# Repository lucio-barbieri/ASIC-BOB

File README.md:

# ASIC-BOB

Break-out board for the RFID+ ASIC.

---

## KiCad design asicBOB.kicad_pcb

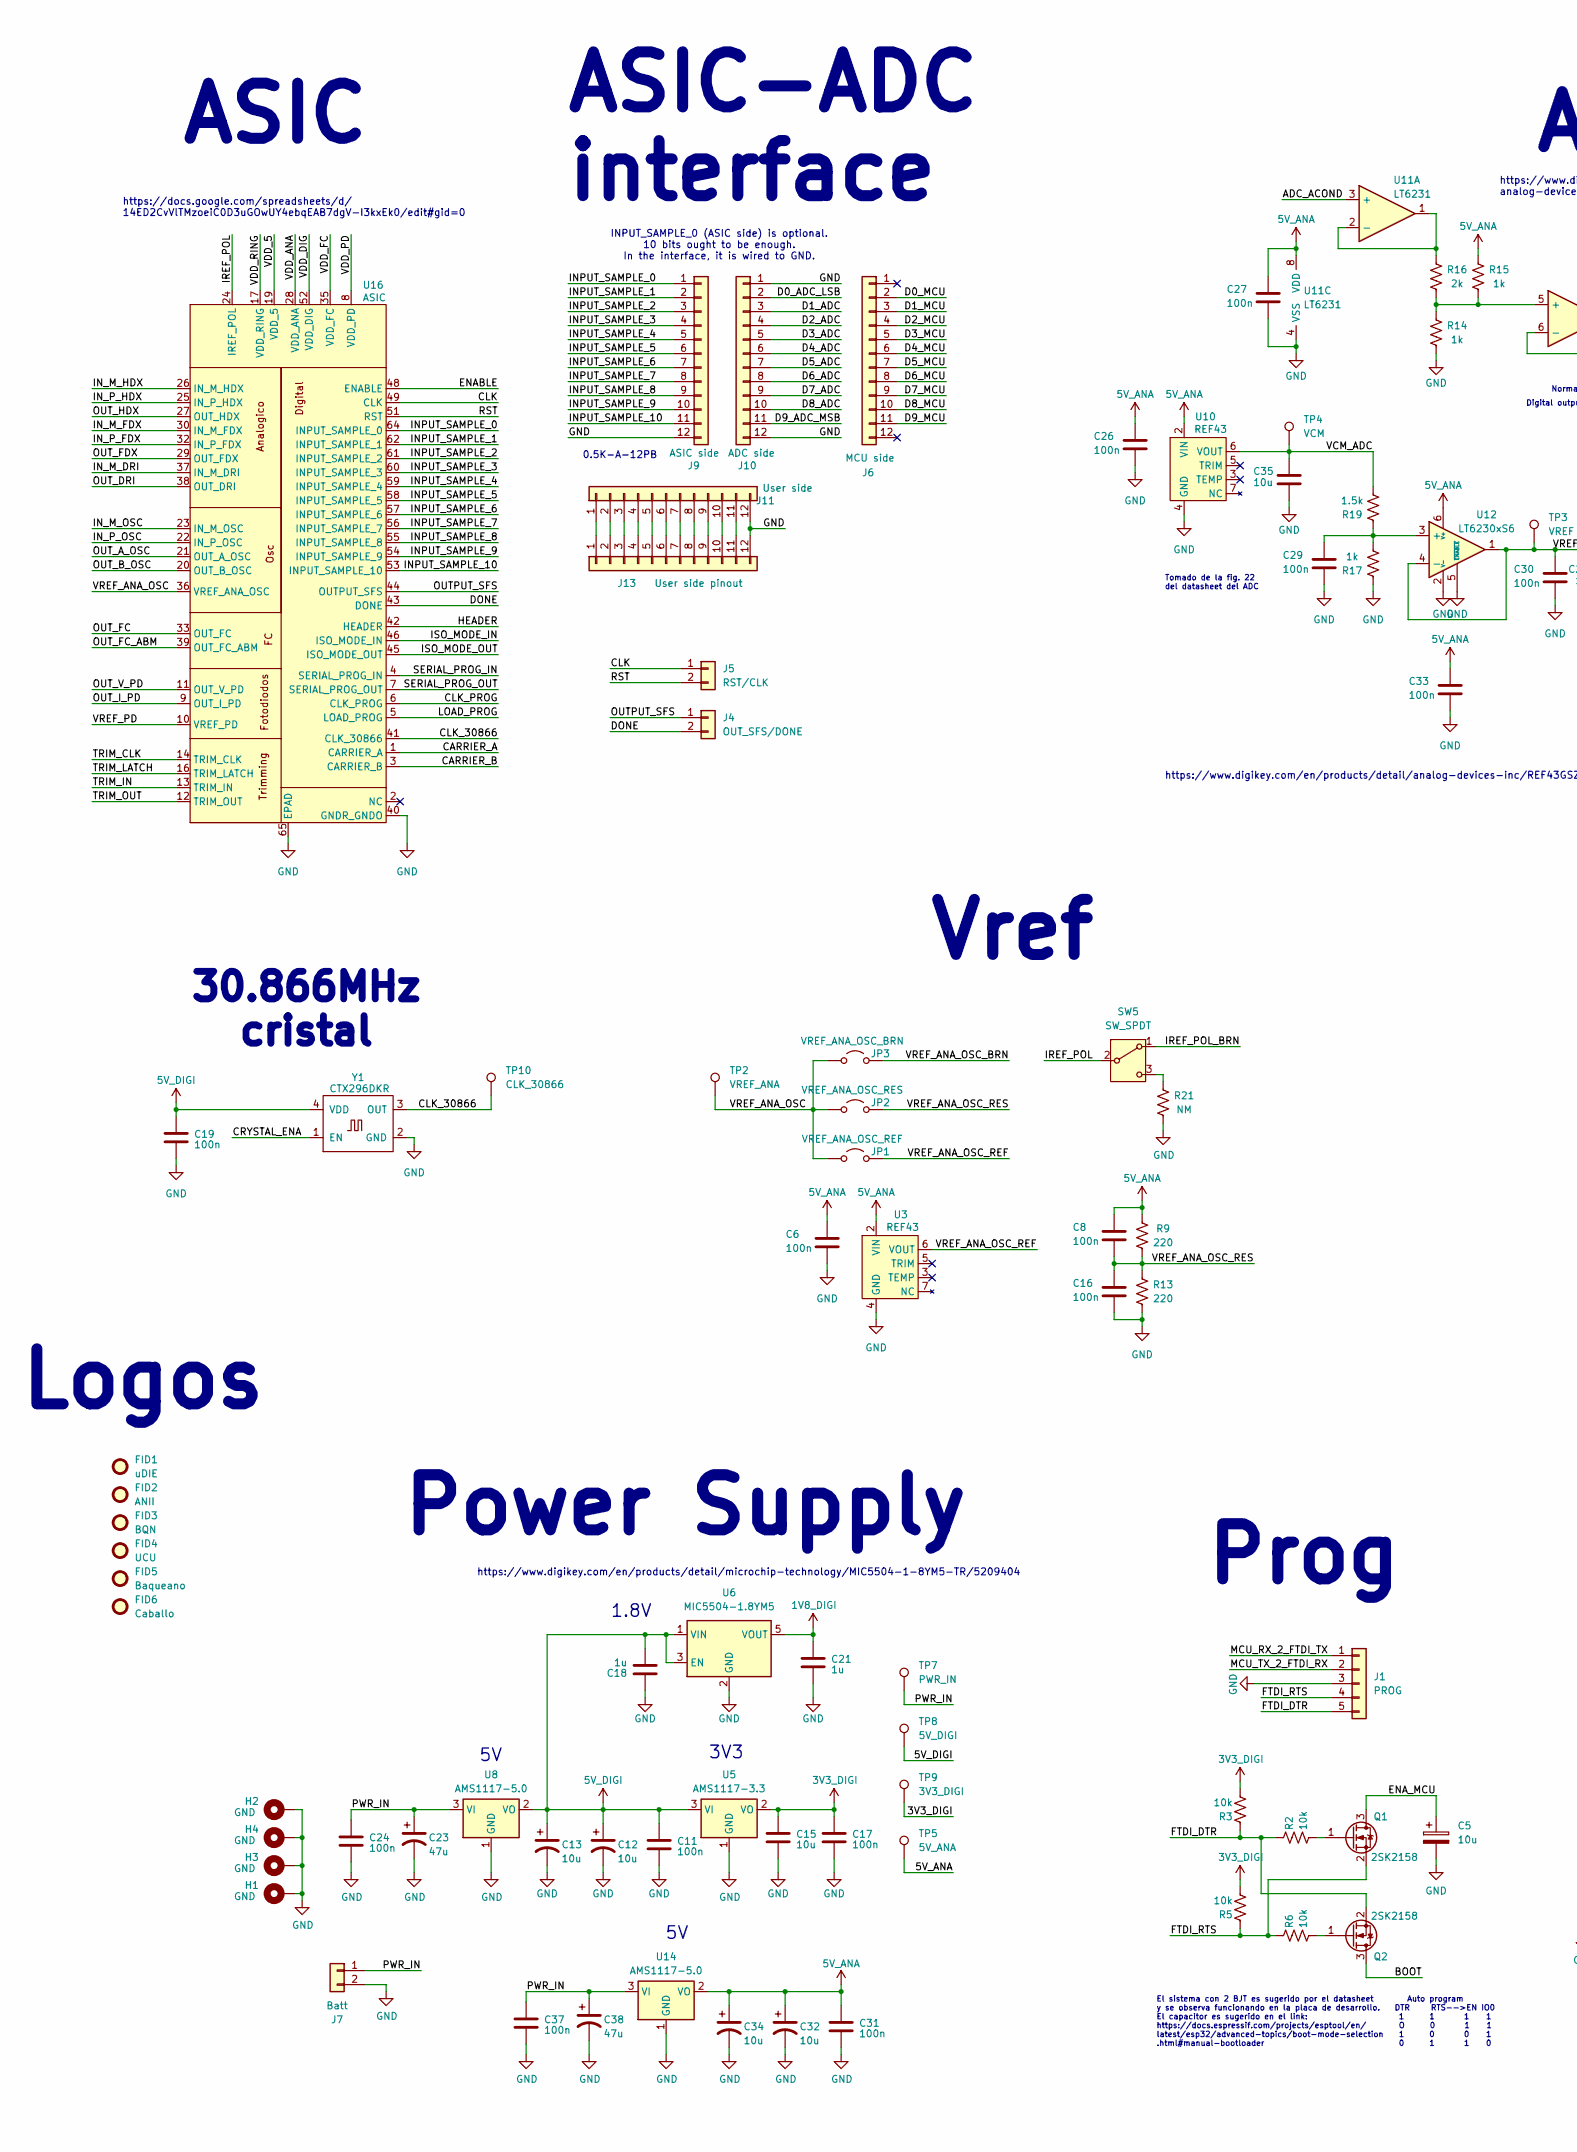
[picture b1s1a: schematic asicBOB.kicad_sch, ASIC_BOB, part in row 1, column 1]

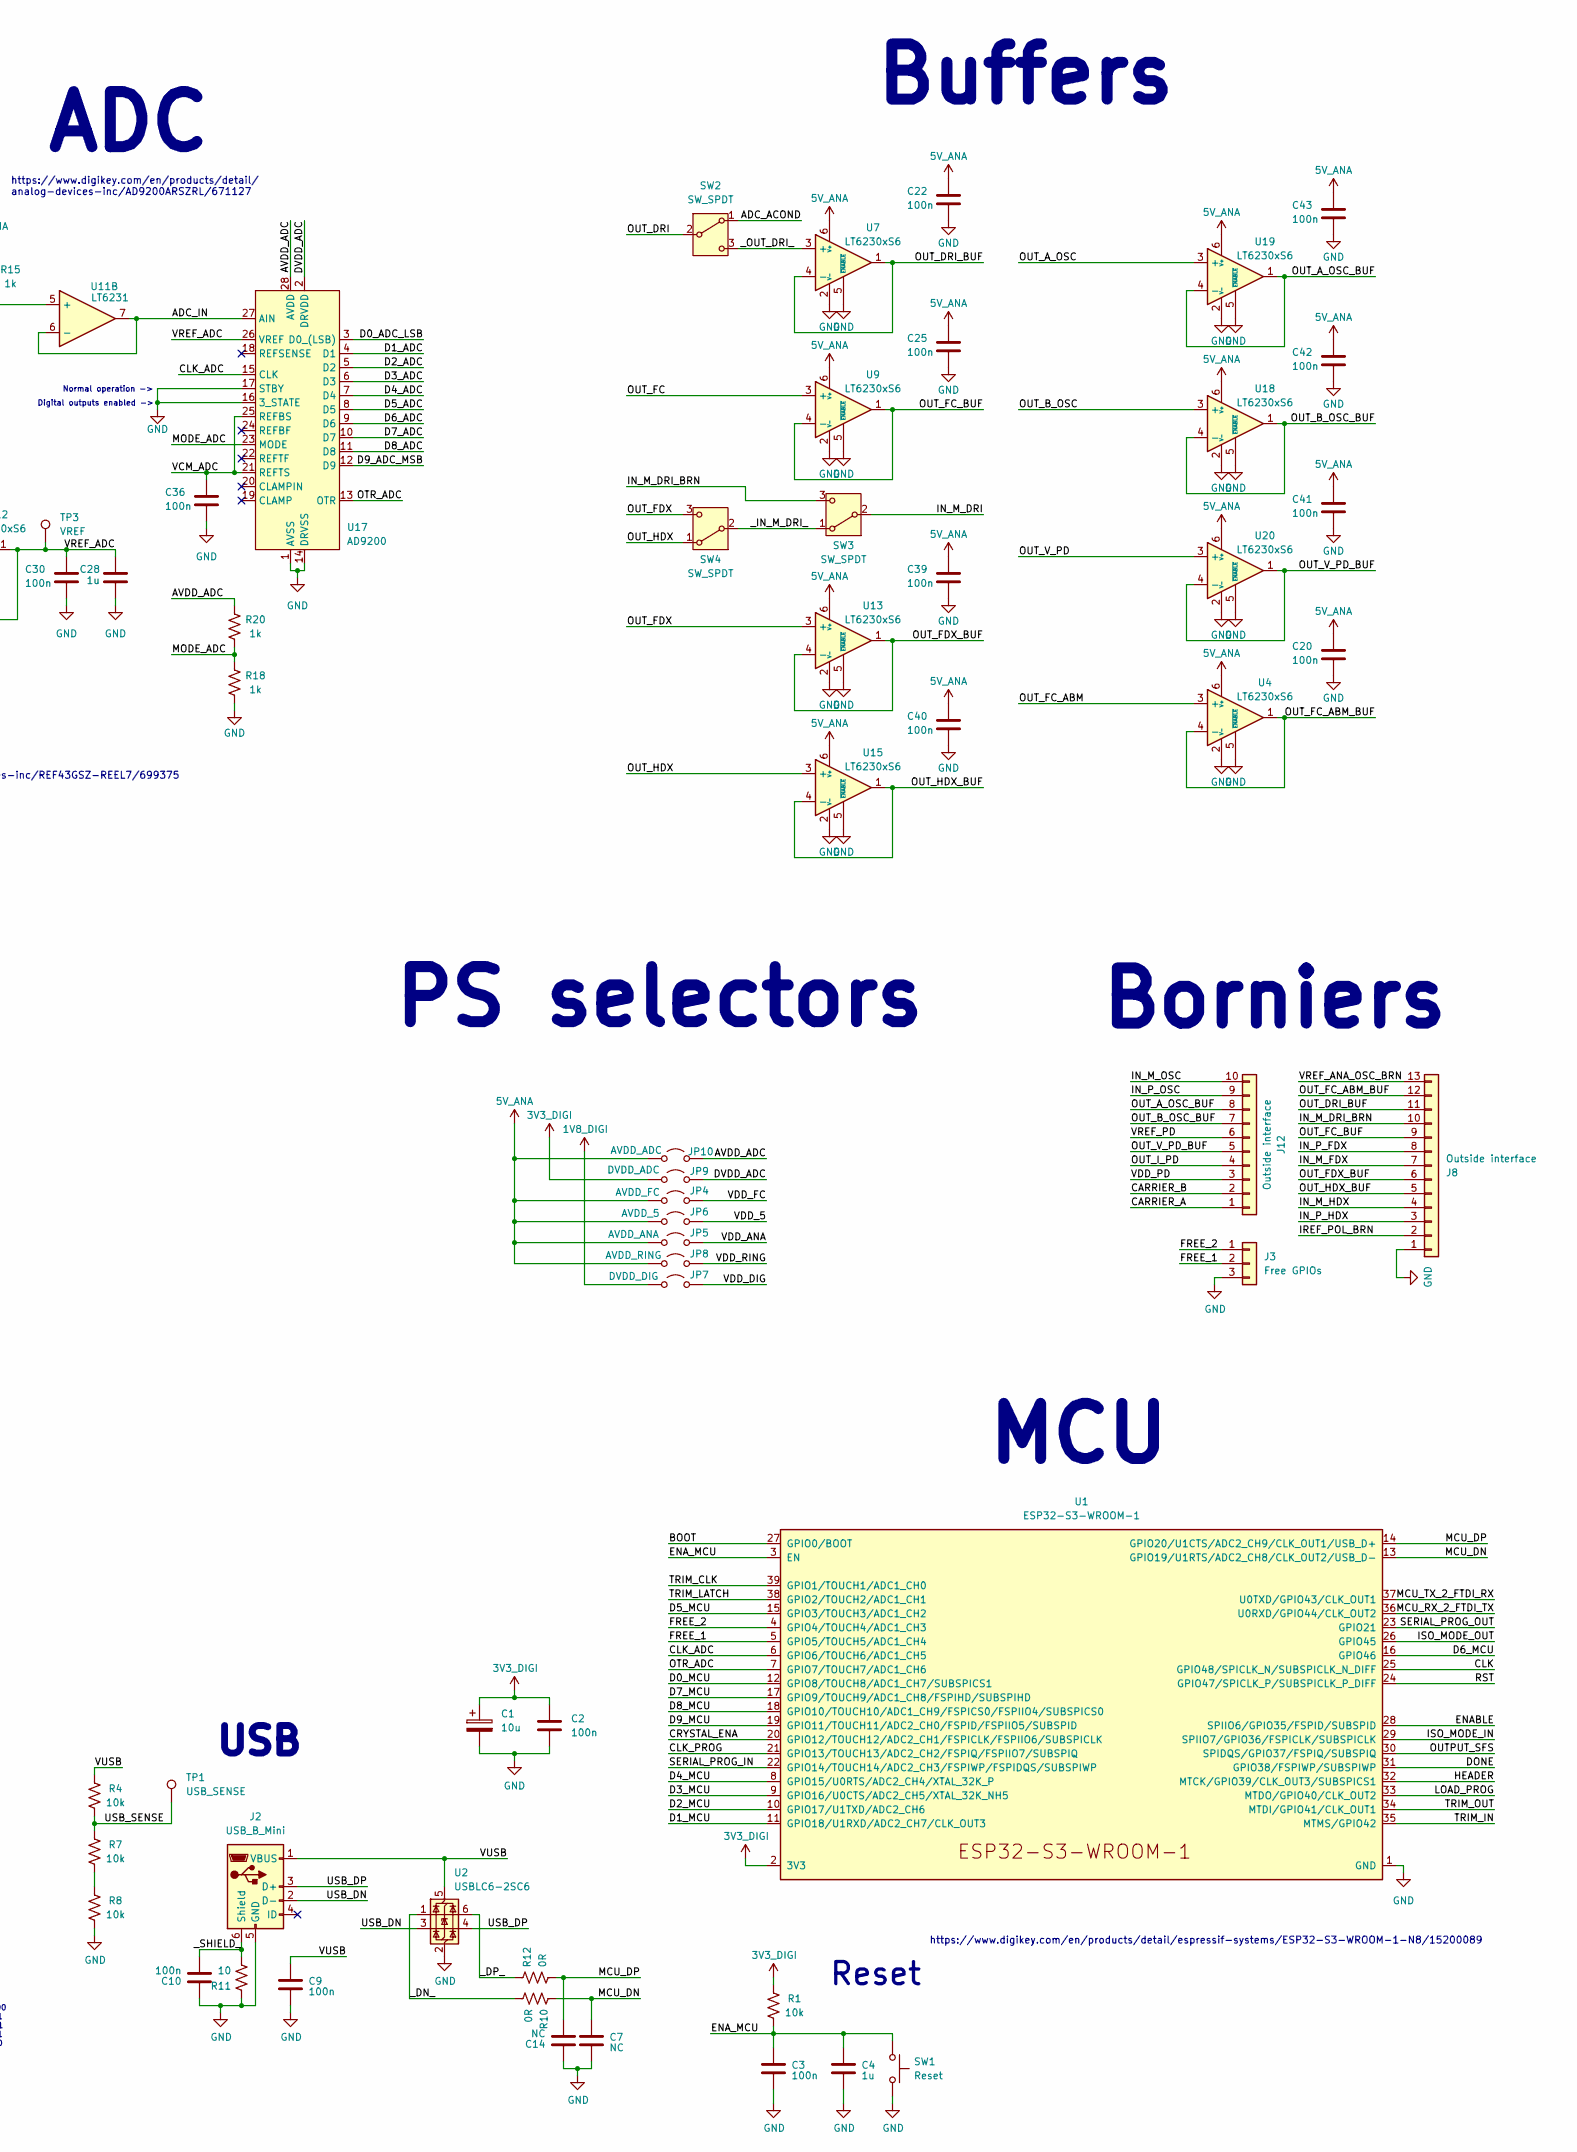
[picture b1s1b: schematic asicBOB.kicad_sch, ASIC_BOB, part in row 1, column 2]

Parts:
C1, C12, C13, C15, C32, C34, C35: 10u; C_0603_1608Metric
C2, C3, C6, C8, C9, C10, C11, C16, C17, C19, C20, C22, C24, C25, C26, C27, C29, C30, C31, C33, C36, C37, C39, C40, C41, C42, C43: 100n; C_0603_1608Metric
C4, C18, C21, C28: 1u; C_0603_1608Metric
C5: 10u; C_1206_3216Metric
C7, C14: NC; C_0603_1608Metric
C23, C38: 47u; C_0805_2012Metric
FID1: uDIE; Logo_uDIE
FID2: ANII; Logo_ANII
FID3: BQN; Logo_BQN_12x4
FID4: UCU; Logo_UCU
FID5: Baqueano; Logo_baqueano_5x25
FID6: Caballo; Logo_caballoConBoina_15mm
H1, H2, H3, H4: GND; MountingHole_2.2mm_M2_Pad_Via
J1: PROG; PinSocket_1x05_P2.54mm_Vertical
J2: USB_B_Mini; USB_Mini-B_Lumberg_2486_01_Horizontal
J3: Free GPIOs; PinHeader_1x03_P2.54mm_Vertical
J4: OUT_SFS/DONE; PinHeader_1x02_P1.27mm_Vertical
J5: RST/CLK; PinHeader_1x02_P1.27mm_Vertical
J6: MCU side; 117347422
J7: Batt; TerminalBlock_Phoenix_MKDS-1,5-2_1x02_P5.00mm_Horizontal
J8: Outside interface; TerminalBlock_Phoenix_MKDS-1,5-13-5.08_1x13_P5.08mm_Horizon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
J9: ASIC side; 117347422
J10: ADC side; 117347422
J11: User side; 117347422
J12: Outside interface; TerminalBlock_Phoenix_MKDS-1,5-10-5.08_1x10_P5.08mm_Horizon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
J13: User side pinout; PinHeader_1x12_P2.54mm_Vertical
JP1: VREF_ANA_OSC_REF; PinHeader_1x02_P2.54mm_Vertical
JP2: VREF_ANA_OSC_RES; PinHeader_1x02_P2.54mm_Vertical
JP3: VREF_ANA_OSC_BRN; PinHeader_1x02_P2.54mm_Vertical
JP4: AVDD_FC; PinHeader_1x02_P2.54mm_Vertical
JP5: AVDD_ANA; PinHeader_1x02_P2.54mm_Vertical
JP6: AVDD_5; PinHeader_1x02_P2.54mm_Vertical
JP7: DVDD_DIG; PinHeader_1x02_P2.54mm_Vertical
JP8: AVDD_RING; PinHeader_1x02_P2.54mm_Vertical
JP9: DVDD_ADC; PinHeader_1x02_P2.54mm_Vertical
JP10: AVDD_ADC; PinHeader_1x02_P2.54mm_Vertical
Q1, Q2: 2SK2158; SOT-23
R1, R2, R3, R4, R5, R6, R7, R8: 10k; R_0603_1608Metric
R9, R13: 220; R_0603_1608Metric
R10, R12: 0R; R_0603_1608Metric
R11: 10; R_0603_1608Metric
R14, R15, R17, R18, R20: 1k; R_0603_1608Metric
R16: 2k; R_0603_1608Metric
R19: 1.5k; R_0603_1608Metric
R21: NM; R_0603_1608Metric
SW1: Reset; SW_Push_1P1T_NO_6x6mm_H9.5mm
SW2, SW3, SW4, SW5: SW_SPDT; PinHeader_1x03_P2.54mm_Vertical
TP1: USB_SENSE; TestPoint_Pad_D1.0mm
TP2: VREF_ANA; TestPoint_Pad_D1.0mm
TP3: VREF; TestPoint_Pad_D1.0mm
TP4: VCM; TestPoint_Pad_D1.0mm
TP5: 5V_ANA; TestPoint_Pad_D1.0mm
TP7: PWR_IN; TestPoint_Pad_D1.0mm
TP8: 5V_DIGI; TestPoint_Pad_D1.0mm
TP9: 3V3_DIGI; TestPoint_Pad_D1.0mm
TP10: CLK_30866; TestPoint_Pad_D1.0mm
U1: ESP32-S3-WROOM-1
U2: USBLC6-2SC6; SOT-23-6
U3, U10: REF43; SOIC-8_3.9x4.9mm_P1.27mm
U4, U7, U9, U12, U13, U15, U18, U19, U20: LT6230xS6; TSOT-23-6
U5: AMS1117-3.3; SOT-223-3_TabPin2
U6: MIC5504-1.8YM5; SOT-23-5
U8, U14: AMS1117-5.0; SOT-223-3_TabPin2
U11: LT6231; SO-8_5.3x6.2mm_P1.27mm
U16: ASIC; ASIC_RFID
U17: AD9200; SSOP-28_5.3x10.2mm_P0.65mm
Y1: CTX296DKR

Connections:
1V8_DIGI: C21.1, JP7.2 (B), U6.5 (VOUT)
3V3_DIGI: C1.1, C2.1, C15.1, C17.1, JP9.2 (B), R1.2, R3.2, R5.2, TP9.1, U1.2 (3V3), U5.2 (VO)
5V_ANA: C6.2, C8.2, C20.2, C22.2, C25.2, C26.2, C27.2, C31.1, C32.1, C33.2, C34.1, C39.2, C40.2, C41.2, C42.2, C43.2, JP4.2 (B), JP5.2 (B), JP6.2 (B), JP8.2 (B), JP10.1 (A), R9.2, R15.2, TP5.1, U3.2 (VIN), U4.6 (V+), U7.6 (V+), U9.6 (V+), U10.2 (VIN), U11.8 (VDD), U12.6 (V+), U13.6 (V+), U14.2 (VO), U15.6 (V+), U18.6 (V+), U19.6 (V+), U20.6 (V+)
5V_DIGI: C11.1, C12.1, C13.1, C18.2, C19.1, TP8.1, U5.3 (VI), U6.1 (VIN), U6.3 (EN), U8.2 (VO), Y1.4 (VDD)
/ADC_ACOND: SW2.1 (A), U11.3 (+)
/ADC_IN: U11.6 (-), U11.7, U17.27 (AIN)
/AVDD_ADC: JP10.2 (B), R20.2, U17.28 (AVDD)
/BOOT: Q2.3 (D), U1.27 (GPIO0/BOOT)
/CARRIER_A: J12.1, U16.1 (CARRIER_A)
/CARRIER_B: J12.2, U16.3 (CARRIER_B)
/CLK: J5.1, U1.25 (GPIO48/SPICLK_N/SUBSPICLK_N_DIFF), U16.49 (CLK)
/CLK_30866: TP10.1, U16.41 (CLK_30866), Y1.3 (OUT)
/CLK_ADC: U1.6 (GPIO6/TOUCH6/ADC1_CH5), U17.15 (CLK)
/CLK_PROG: U1.21 (GPIO13/TOUCH13/ADC2_CH2/FSPIQ/FSPIIO7/S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), U16.6 (CLK_PROG)
/CRYSTAL_ENA: U1.20 (GPIO12/TOUCH12/ADC2_CH1/FSPICLK/FSPIIO6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), Y1.1 (EN)
/D0_ADC_LSB: J10.2, U17.3 (D0_(LSB))
/D0_MCU: J6.2, U1.12 (GPIO8/TOUCH8/ADC1_CH7/SUBSPICS1)
/D1_ADC: J10.3, U17.4 (D1)
/D1_MCU: J6.3, U1.11 (GPIO18/U1RXD/ADC2_CH7/CLK_OUT3)
/D2_ADC: J10.4, U17.5 (D2)
/D2_MCU: J6.4, U1.10 (GPIO17/U1TXD/ADC2_CH6)
/D3_ADC: J10.5, U17.6 (D3)
/D3_MCU: J6.5, U1.9 (GPIO16/U0CTS/ADC2_CH5/XTAL_32K_NH5)
/D4_ADC: J10.6, U17.7 (D4)
/D4_MCU: J6.6, U1.8 (GPIO15/U0RTS/ADC2_CH4/XTAL_32K_P)
/D5_ADC: J10.7, U17.8 (D5)
/D5_MCU: J6.7, U1.15 (GPIO3/TOUCH3/ADC1_CH2)
/D6_ADC: J10.8, U17.9 (D6)
/D6_MCU: J6.8, U1.16 (GPIO46)
/D7_ADC: J10.9, U17.10 (D7)
/D7_MCU: J6.9, U1.17 (GPIO9/TOUCH9/ADC1_CH8/FSPIHD/SUBSPIHD)
/D8_ADC: J10.10, U17.11 (D8)
/D8_MCU: J6.10, U1.18 (GPIO10/TOUCH10/ADC1_CH9/FSPICS0/FSPIIO4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)
/D9_ADC_MSB: J10.11, U17.12 (D9)
/D9_MCU: J6.11, U1.19 (GPIO11/TOUCH11/ADC2_CH0/FSPID/FSPIIO5/S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)
/DONE: J4.2, U1.31 (GPIO38/FSPIWP/SUBSPIWP), U16.43 (DONE)
/DVDD_ADC: JP9.1 (A), U17.2 (DRVDD)
/ENABLE: U1.28 (SPIIO6/GPIO35/FSPID/SUBSPID), U16.48 (ENABLE)
/ENA_MCU: C3.1, C4.1, C5.1, Q1.3 (D), R1.1, SW1.1, U1.3 (EN)
/FREE_1: J3.2, U1.5 (GPIO5/TOUCH5/ADC1_CH4)
/FREE_2: J3.1, U1.4 (GPIO4/TOUCH4/ADC1_CH3)
/FTDI_DTR: J1.5, Q2.2 (S), R2.1, R3.1
/FTDI_RTS: J1.4, Q1.2 (S), R5.1, R6.1
/HEADER: U1.32 (MTCK/GPIO39/CLK_OUT3/SUBSPICS1), U16.42 (HEADER)
/INPUT_SAMPLE_0: J9.1, U16.64 (INPUT_SAMPLE_0)
/INPUT_SAMPLE_1: J9.2, U16.62 (INPUT_SAMPLE_1)
/INPUT_SAMPLE_2: J9.3, U16.61 (INPUT_SAMPLE_2)
/INPUT_SAMPLE_3: J9.4, U16.60 (INPUT_SAMPLE_3)
/INPUT_SAMPLE_4: J9.5, U16.59 (INPUT_SAMPLE_4)
/INPUT_SAMPLE_5: J9.6, U16.58 (INPUT_SAMPLE_5)
/INPUT_SAMPLE_6: J9.7, U16.57 (INPUT_SAMPLE_6)
/INPUT_SAMPLE_7: J9.8, U16.56 (INPUT_SAMPLE_7)
/INPUT_SAMPLE_8: J9.9, U16.55 (INPUT_SAMPLE_8)
/INPUT_SAMPLE_9: J9.10, U16.54 (INPUT_SAMPLE_9)
/INPUT_SAMPLE_10: J9.11, U16.53 (INPUT_SAMPLE_10)
/IN_M_DRI: SW3.2 (B), U16.37 (IN_M_DRI)
/IN_M_DRI_BRN: J8.10, SW3.3 (C)
/IN_M_FDX: J8.7, U16.30 (IN_M_FDX)
/IN_M_HDX: J8.4, U16.26 (IN_M_HDX)
/IN_M_OSC: J12.10, U16.23 (IN_M_OSC)
/IN_P_FDX: J8.8, U16.32 (IN_P_FDX)
/IN_P_HDX: J8.3, U16.25 (IN_P_HDX)
/IN_P_OSC: J12.9, U16.22 (IN_P_OSC)
/IREF_POL: SW5.2 (B), U16.24 (IREF_POL)
/IREF_POL_BRN: J8.2, SW5.1 (A)
/ISO_MODE_IN: U1.29 (SPIIO7/GPIO36/FSPICLK/SUBSPICLK), U16.46 (ISO_MODE_IN)
/ISO_MODE_OUT: U1.26 (GPIO45), U16.45 (ISO_MODE_OUT)
/LOAD_PROG: U1.33 (MTDO/GPIO40/CLK_OUT2), U16.5 (LOAD_PROG)
/MCU_DN: C7.1, R10.1, U1.13 (GPIO19/U1RTS/ADC2_CH8/CLK_OUT2/USB_D-)
/MCU_DP: C14.2, R12.2, U1.14 (GPIO20/U1CTS/ADC2_CH9/CLK_OUT1/USB_D+)
/MCU_RX_2_FTDI_TX: J1.1, U1.36 (U0RXD/GPIO44/CLK_OUT2)
/MCU_TX_2_FTDI_RX: J1.2, U1.37 (U0TXD/GPIO43/CLK_OUT1)
/MODE_ADC: R18.2, R20.1, U17.23 (MODE)
/OTR_ADC: U1.7 (GPIO7/TOUCH7/ADC1_CH6), U17.13 (OTR)
/OUTPUT_SFS: J4.1, U1.30 (SPIDQS/GPIO37/FSPIQ/SUBSPIQ), U16.44 (OUTPUT_SFS)
/OUT_A_OSC: U16.21 (OUT_A_OSC), U19.3 (+)
/OUT_A_OSC_BUF: J12.8, U19.1, U19.4 (-)
/OUT_B_OSC: U16.20 (OUT_B_OSC), U18.3 (+)
/OUT_B_OSC_BUF: J12.7, U18.1, U18.4 (-)
/OUT_DRI: SW2.2 (B), U16.38 (OUT_DRI)
/OUT_DRI_BUF: J8.11, U7.1, U7.4 (-)
/OUT_FC: U9.3 (+), U16.33 (OUT_FC)
/OUT_FC_ABM: U4.3 (+), U16.39 (OUT_FC_ABM)
/OUT_FC_ABM_BUF: J8.12, U4.1, U4.4 (-)
/OUT_FC_BUF: J8.9, U9.1, U9.4 (-)
/OUT_FDX: SW4.3 (C), U13.3 (+), U16.29 (OUT_FDX)
/OUT_FDX_BUF: J8.6, U13.1, U13.4 (-)
/OUT_HDX: SW4.1 (A), U15.3 (+), U16.27 (OUT_HDX)
/OUT_HDX_BUF: J8.5, U15.1, U15.4 (-)
/OUT_I_PD: J12.4, U16.9 (OUT_I_PD)
/OUT_V_PD: U16.11 (OUT_V_PD), U20.3 (+)
/OUT_V_PD_BUF: J12.5, U20.1, U20.4 (-)
/PWR_IN: C23.1, C24.1, C37.1, C38.1, J7.1, TP7.1, U8.3 (VI), U14.3 (VI)
/RST: J5.2, U1.24 (GPIO47/SPICLK_P/SUBSPICLK_P_DIFF), U16.51 (RST)
/SERIAL_PROG_IN: U1.22 (GPIO14/TOUCH14/ADC2_CH3/FSPIWP/FSPIDQS/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), U16.4 (SERIAL_PROG_IN)
/SERIAL_PROG_OUT: U1.23 (GPIO21), U16.7 (SERIAL_PROG_OUT)
/TRIM_CLK: U1.39 (GPIO1/TOUCH1/ADC1_CH0), U16.14 (TRIM_CLK)
/TRIM_IN: U1.35 (MTMS/GPIO42), U16.13 (TRIM_IN)
/TRIM_LATCH: U1.38 (GPIO2/TOUCH2/ADC1_CH1), U16.16 (TRIM_LATCH)
/TRIM_OUT: U1.34 (MTDI/GPIO41/CLK_OUT1), U16.12 (TRIM_OUT)
/USB_DN: J2.2 (D-), U2.3 (I/O2)
/USB_DP: J2.3 (D+), U2.4 (I/O2)
/USB_SENSE: R4.1, R7.2, TP1.1
/VCM_ADC: C35.2, C36.2, R19.1, TP4.1, U10.6 (VOUT), U17.21 (REFTS), U17.25 (REFBS)
/VDD_5: JP6.1 (A), U16.19 (VDD_5)
/VDD_ANA: JP5.1 (A), U16.28 (VDD_ANA)
/VDD_DIG: JP7.1 (A), U16.52 (VDD_DIG)
/VDD_FC: JP4.1 (A), U16.35 (VDD_FC)
/VDD_PD: J12.3, U16.8 (VDD_PD)
/VDD_RING: JP8.1 (A), U16.17 (VDD_RING)
/VREF_ADC: C28.2, C30.2, TP3.1, U12.1, U12.4 (-), U17.26 (VREF)
/VREF_ANA_OSC: JP1.1 (A), JP2.1 (A), JP3.1 (A), TP2.1, U16.36 (VREF_ANA_OSC)
/VREF_ANA_OSC_BRN: J8.13, JP3.2 (B)
/VREF_ANA_OSC_REF: JP1.2 (B), U3.6 (VOUT)
/VREF_ANA_OSC_RES: C8.1, C16.2, JP2.2 (B), R9.1, R13.2
/VREF_PD: J12.6, U16.10 (VREF_PD)
/VUSB: C9.1, J2.1 (VBUS), R4.2, U2.5 (VBUS)
/_DN_: R10.2, U2.1 (I/O1)
/_DP_: R12.1, U2.6 (I/O1)
/_IN_M_DRI_: SW3.1 (A), SW4.2 (B)
/_OUT_DRI_: SW2.3 (C), U7.3 (+)
/_SHIELD_: C10.2, J2.6 (Shield), R11.2
GND: C1.2, C2.2, C3.2, C4.2, C5.2, C6.1, C7.2, C9.2, C10.1, C11.2, C12.2, C13.2, C14.1, C15.2, C16.1, C17.2, C18.1, C19.2, C20.1, C21.2, C22.1, C23.2, C24.2, C25.1, C26.1, C27.1, C28.1, C29.1, C30.1, C31.2, C32.2, C33.1, C34.2, C35.1, C36.1, C37.2, C38.2, C39.1, C40.1, C41.1, C42.1, C43.1, H1.1, H2.1, H3.1, H4.1, J1.3, J2.5 (GND), J3.3, J7.2, J8.1, J9.12, J10.1, J10.12, J11.12, J13.12, R8.1, R11.1, R13.1, R14.1, R17.2, R18.1, R21.1, SW1.2, U1.1 (GND), U1.40 (GND), U1.41 (GND), U2.2 (GND), U3.4 (GND), U4.2 (V-), U4.5 (~ENABLE), U5.1 (GND), U6.2 (GND), U7.2 (V-), U7.5 (~ENABLE), U8.1 (GND), U9.2 (V-), U9.5 (~ENABLE), U10.4 (GND), U11.4 (VSS), U12.2 (V-), U12.5 (~ENABLE), U13.2 (V-), U13.5 (~ENABLE), U14.1 (GND), U15.2 (V-), U15.5 (~ENABLE), U16.40 (GNDR_GNDO), U16.65 (EPAD), U17.1 (AVSS), U17.14 (DRVSS), U17.16 (3_STATE), U17.17 (STBY), U18.2 (V-), U18.5 (~ENABLE), U19.2 (V-), U19.5 (~ENABLE), U20.2 (V-), U20.5 (~ENABLE), Y1.2 (GND)
unnamed: J11.1, J13.1
unnamed: J11.2, J13.2
unnamed: J11.3, J13.3
unnamed: J11.4, J13.4
unnamed: J11.5, J13.5
unnamed: J11.6, J13.6
unnamed: J11.7, J13.7
unnamed: J11.8, J13.8
unnamed: J11.9, J13.9
unnamed: J11.10, J13.10
unnamed: J11.11, J13.11
unnamed: Q1.1 (G), R2.2
unnamed: Q2.1 (G), R6.2
unnamed: R7.1, R8.2
unnamed: R21.2, SW5.3 (C)
unnamed: R16.2, U11.1, U11.2 (-)
unnamed: R14.2, R15.1, R16.1, U11.5 (+)
unnamed: C29.2, R17.1, R19.2, U12.3 (+)

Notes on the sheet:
0.5K-A-12PB
Logos
INPUT_SAMPLE_0 (ASIC side) is optional. 10 bits ought to be enough. In the interface, it is wired to GND.
ADC
ASIC-ADC interface
3V3
https://www.digikey.com/en/products/detail/analog-devices-inc/REF43GSZ-REEL7/699375
https://www.digikey.com/en/products/detail/microchip-technology/MIC5504-1-8YM5-TR/5209404
USB
https://www.digikey.com/en/products/detail/espressif-systems/ESP32-S3-WROOM-1-N8/15200089
Auto program DTR RTS-->EN IO0 1 1 1 1 O 0 1 1 1 0 0 1 0 1 1 0
ASIC
Tomado de la fig. 22 del datasheet del ADC
Reset
Prog
Power Supply
El sistema con 2 BJT es sugerido por el datasheet y se observa funcionando en la placa de desarrollo. El capacitor es sugerido en el link: https://docs.espressif.com/projects/esptool/en/ latest/esp32/advanced-topics/boot-mode-selection .html#manual-bootloader
https://www.digikey.com/en/products/detail/ analog-devices-inc/AD9200ARSZRL/671127
https://docs.google.com/spreadsheets/d/ 14ED2CvVlTMzoeiC0D3uGOwUY4ebqEAB7dgV-I3kxEk0/edit#gid=0
Buffers
Vref
1.8V
PS selectors
30.866MHz cristal
Normal operation ->
Digital outputs enabled ->
MCU
Borniers

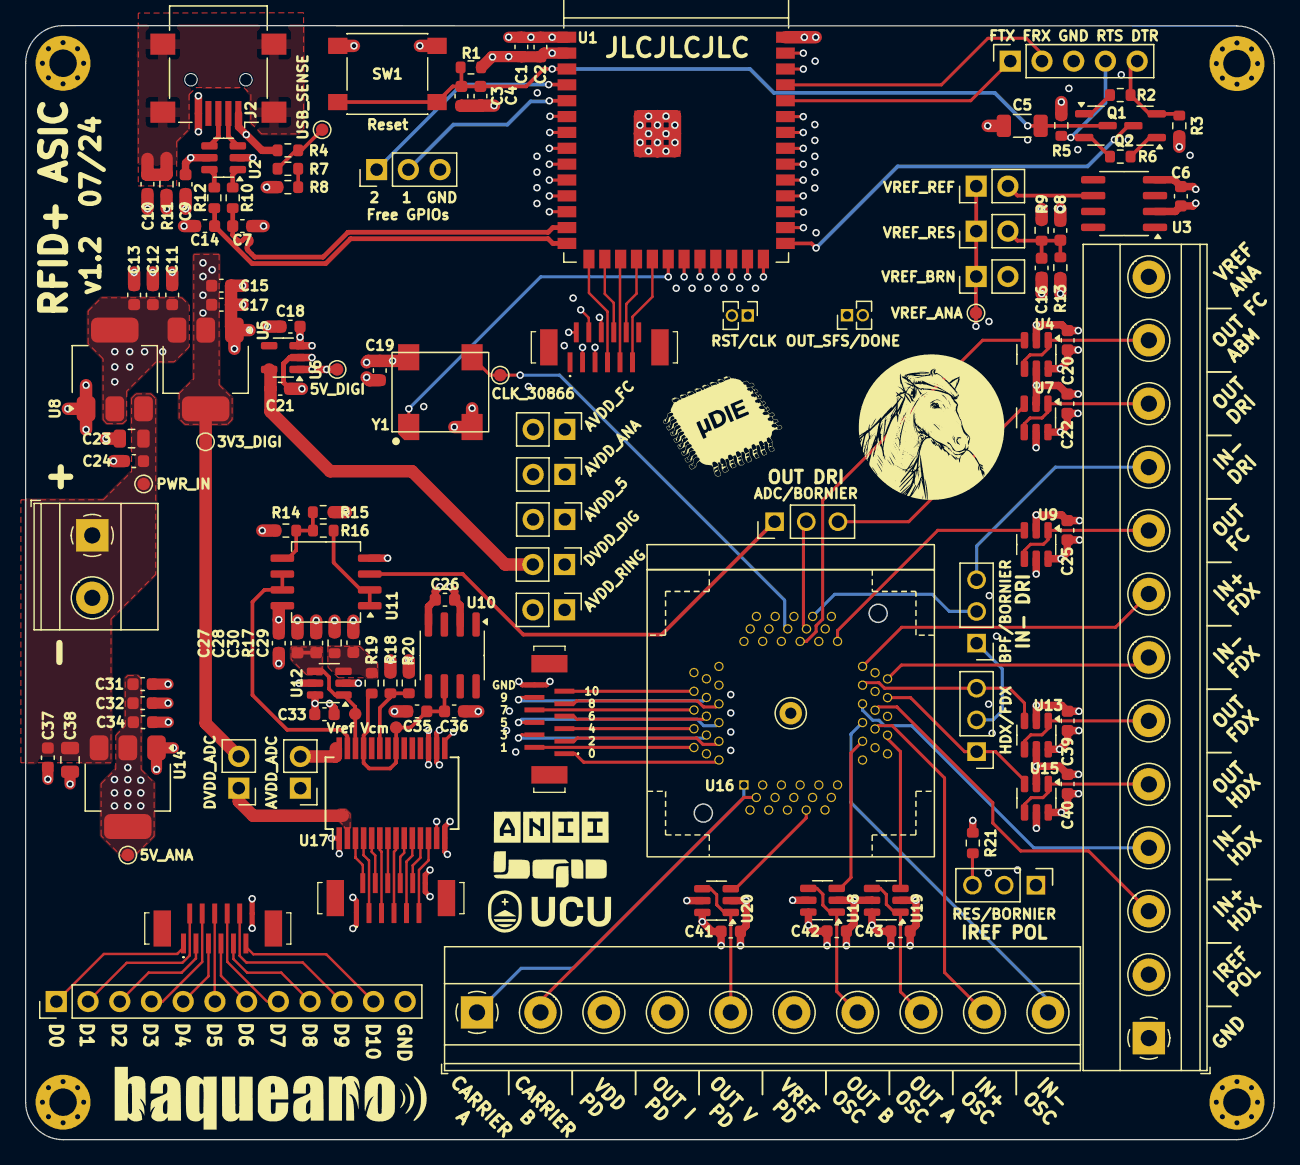
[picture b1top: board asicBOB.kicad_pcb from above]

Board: 6 copper layers, 100.0 x 89.2 mm, 134 parts (0 on the bottom side), 141 nets.

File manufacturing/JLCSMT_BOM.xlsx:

Designator | Footprint | Quantity | Comment | LCSC Part # (optional)
C1, C12, C13, C15, C32, C34, C35 | 0603 | 7 | 10u | C19702
C10, C11, C16, C17, C19, C2, C20, C22, C24, C25, C26, C27, C29, C3, C30, C31, C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 | 0603 | 27 | 100n | C14663
C18, C21, C28, C4 | 0603 | 4 | 1u | C108463
C23, C38 | 0805 | 2 | 47u | C108659
C5 | 1206 | 1 | 10u | C13585
J12 | TerminalBlock_Phoenix_MKDS-1,5-10-5.08_1x10_P5.08mm_Horizontal | 1 | Outside interface
J2 | USB_Mini-B_Lumberg_2486_01_Horizontal | 1 | USB_B_Mini | C2681563
J4, J5 | PinHeader_1x02_P1.27mm_Vertical | 2 | OUT_SFS/DONE, RST/CLK | C2881948
J6, J9, J10, J11 | 117347422 | 4 | MCU side, ASIC side, ADC side, User side | C590853
J7 | TerminalBlock_Phoenix_MKDS-1,5-2_1x02_P5.00mm_Horizontal | 1 | Batt | C8404
J8 | TerminalBlock_Phoenix_MKDS-1,5-13-5.08_1x13_P5.08mm_Horizontal | 1 | Outside interface
Q1, Q2 | SOT-23 | 2 | 2SK2158 | C130894
R1, R2, R3, R4, R5, R6, R7, R8 | 0603 | 8 | 10k | C25804
R10, R12 | 0603 | 2 | 0R | C21189
R11 | 0603 | 1 | 10 | C22859
R13, R9 | 0603 | 2 | 220 | C22962
R14, R15, R17, R18, R20 | 0603 | 5 | 1k | C21190
R16 | 0603 | 1 | 2k | C22975
R19 | 0603 | 1 | 1.5k | C101276
SW1 | SW_Push_1P1T_NO_6x6mm_H9.5mm | 1 | Reset | C285446
U1 | ESP32-S3-WROOM-1 | 1 | ESP32-S3-WROOM-1 | C2913199
U10, U3 | SOIC-8_3.9x4.9mm_P1.27mm | 2 | REF43
U11 | SO-8_5.3x6.2mm_P1.27mm | 1 | LT6231 | C580237
U12, U13, U15, U18, U19, U20, U4, U7, U9 | TSOT-23-6 | 9 | LT6230xS6 | C580235
U14, U8 | SOT-223-3_TabPin2 | 2 | AMS1117-5.0 | C6187
U17 | SSOP-28_5.3x10.2mm_P0.65mm | 1 | AD9200 | C207693
U2 | SOT-23-6 | 1 | USBLC6-2SC6 | C2827654
U5 | SOT-223-3_TabPin2 | 1 | AMS1117-3.3 | C347222
U6 | SOT-23-5 | 1 | MIC5504-1.8YM5 | C626116

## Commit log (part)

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2024-06-28 Primer commit.
2024-06-28 Version casi completa, con USB, sin UART.
2024-06-28 Version con dos USBs, uno con FTDI y otro USB mismo.
2024-06-28 Agrego pinout para FTDI BOB
2024-07-11 Agrego programacion.
